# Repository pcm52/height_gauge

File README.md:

# height_gauge
Digital Height Gauge

Design files for digital height gauge as described on pcm52.com

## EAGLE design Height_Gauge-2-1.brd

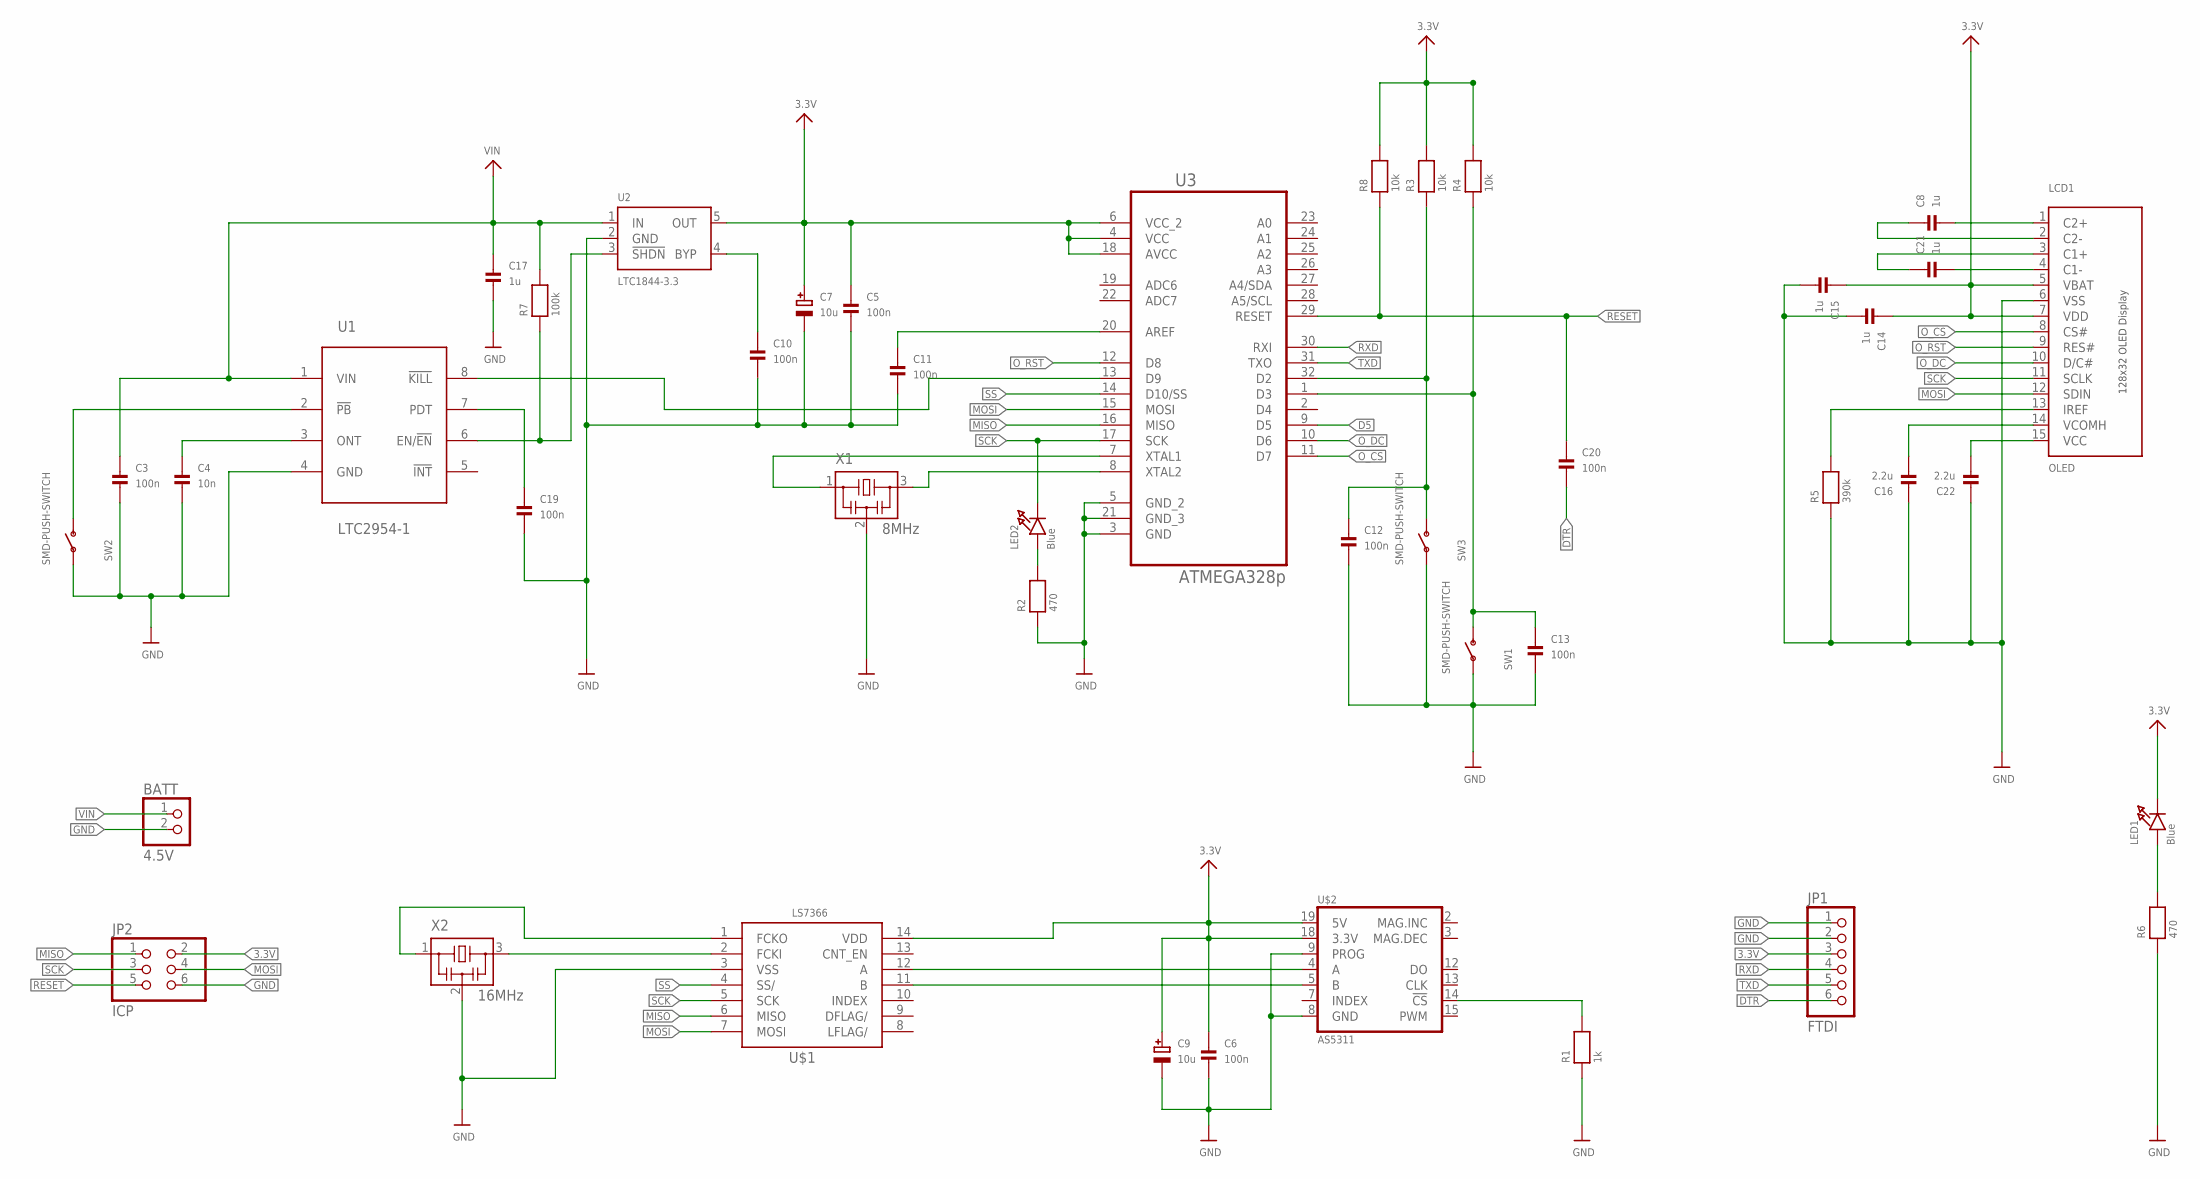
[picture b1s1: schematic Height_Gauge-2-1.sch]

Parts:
BATT: 4.5V; 1X02
C3, C5, C6, C10, C11, C12, C13, C19, C20: 100n; 0805
C4: 10n; 0805
C7, C9: 10u; EIA3216-18/A-W
C8, C14, C15, C17, C21: 1u; 0805
C16, C22: 2.2u; 0805
JP1: FTDI; 1X06-BIG
JP2: ICP; 2X03
LCD1: OLED; UG-2832HSWEG04_WRAPAROUND
LED1, LED2: Blue; CHIPLED_0805
R1: 1k; 0805
R2, R6: 470; 0805
R3, R4, R8: 10k; 0805
R5: 390k; 0805
R7: 100k; 0805
SW1, SW2, SW3: SMD-PUSH-SWITCH; PUSH-BUTTON-SMD
U1: LTC2954-1; TSOT23-8
U2: LTC1844-3.3; TSOT23-5
U3: ATMEGA328p; TQFP-32
U$1: LS7366; SO14
U$2: AS5311; TSSOP.20
X1: 8MHz; CSTCE-CRYSTAL-OSC
X2: 16MHz; CSTCE-CRYSTAL-OSC

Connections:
3.3V: C5.1, C6.1, C7.+, C9.+, C14.1, C15.1, JP1.3, JP2.2, LCD1.5 (VBAT), LCD1.7 (VDD), LED1.C, R3.2, R4.2, R8.2, U2.5 (OUT), U3.4 (VCC), U3.6 (VCC_2), U3.18 (AVCC), U$1.14 (VDD), U$2.18 (3.3V), U$2.19 (5V)
D5: U3.9 (D5)
DTR: C20.2, JP1.6
GND: BATT.2, C3.2, C4.2, C5.2, C6.2, C7.-, C9.-, C10.2, C11.2, C12.2, C13.2, C14.2, C15.2, C16.1, C17.2, C19.2, C22.1, JP1.1, JP1.2, JP2.6, LCD1.6 (VSS), R1.1, R2.1, R5.1, R6.1, SW1.P$1, SW2.P$1, SW3.P$1, U1.4 (GND), U2.2 (GND), U3.3 (GND), U3.5 (GND_2), U3.21 (GND_3), U$1.3 (VSS), U$2.8 (GND), U$2.9 (PROG), X1.2, X2.2
KILL: U1.8 (!KILL), U3.13 (D9)
MISO: JP2.1, U3.16 (MISO), U$1.6 (MISO)
MOSI: JP2.4, LCD1.12 (SDIN), U3.15 (MOSI), U$1.7 (MOSI)
unnamed: U$1.2 (FCKI), X2.3
unnamed: U$1.1 (FCKO), X2.1
unnamed: R7.1, U1.6 (EN/!EN), U2.3 (!SHDN)
unnamed: R1.2, U$2.14 (!CS)
unnamed: SW2.P$2 (S), U1.2 (!PB)
unnamed: U$1.12 (A), U$2.4 (A)
unnamed: U$1.11 (B), U$2.5 (B)
unnamed: C4.1, U1.3 (ONT)
unnamed: C10.1, U2.4 (BYP)
unnamed: C11.1, U3.20 (AREF)
unnamed: C12.1, R3.1, SW3.P$2 (S), U3.32 (D2)
unnamed: U3.7 (XTAL1), X1.1
unnamed: U3.8 (XTAL2), X1.3
unnamed: C13.1, R4.1, SW1.P$2 (S), U3.1 (D3)
unnamed: LED2.A, R2.2
unnamed: C8.2, LCD1.1 (C2+)
unnamed: LED1.A, R6.2
unnamed: C19.1, U1.7 (PDT)
unnamed: C8.1, LCD1.2 (C2-)
unnamed: C21.2, LCD1.4 (C1-)
unnamed: C21.1, LCD1.3 (C1+)
unnamed: LCD1.13 (IREF), R5.2
unnamed: C16.2, LCD1.14 (VCOMH)
unnamed: C22.2, LCD1.15 (VCC)
O_CS: LCD1.8 (CS#), U3.11 (D7)
O_DC: LCD1.10 (D/C#), U3.10 (D6)
O_RST: LCD1.9 (RES#), U3.12 (D8)
RESET: C20.1, JP2.5, R8.1, U3.29 (RESET)
RXD: JP1.4, U3.30 (RXI)
SCK: JP2.3, LCD1.11 (SCLK), LED2.C, U3.17 (SCK), U$1.5 (SCK)
SS: U3.14 (D10/SS), U$1.4 (SS/)
TXD: JP1.5, U3.31 (TXO)
VIN: BATT.1, C3.1, C17.1, R7.2, U1.1 (VIN), U2.1 (IN)

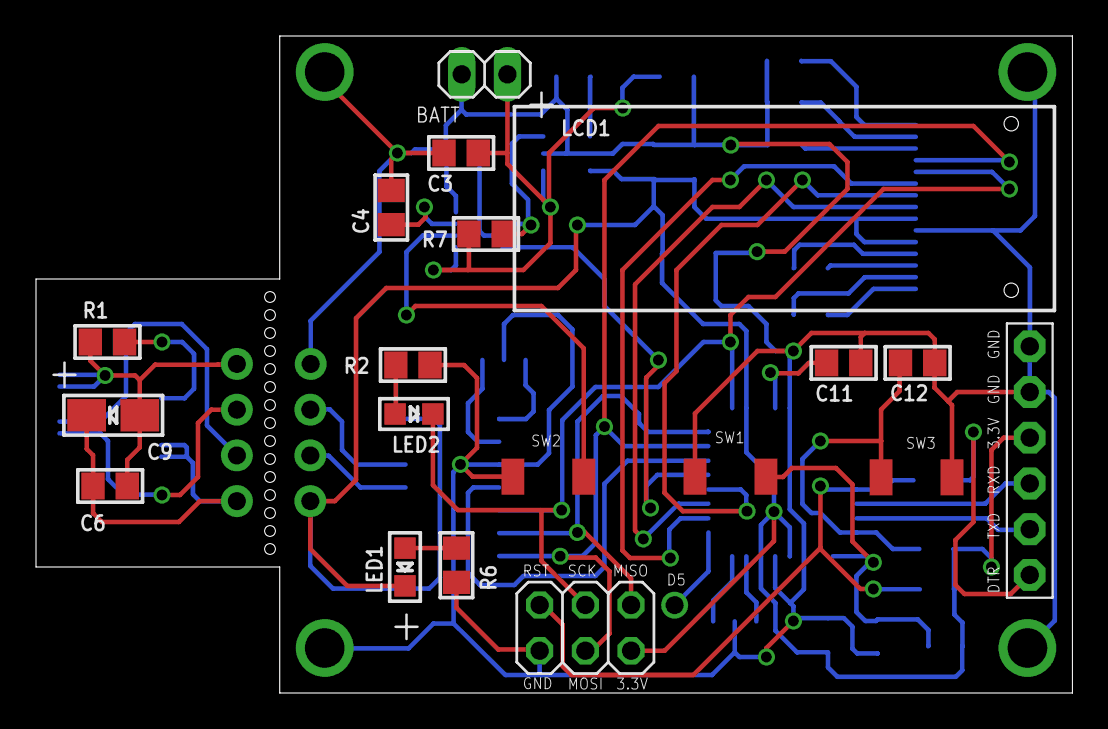
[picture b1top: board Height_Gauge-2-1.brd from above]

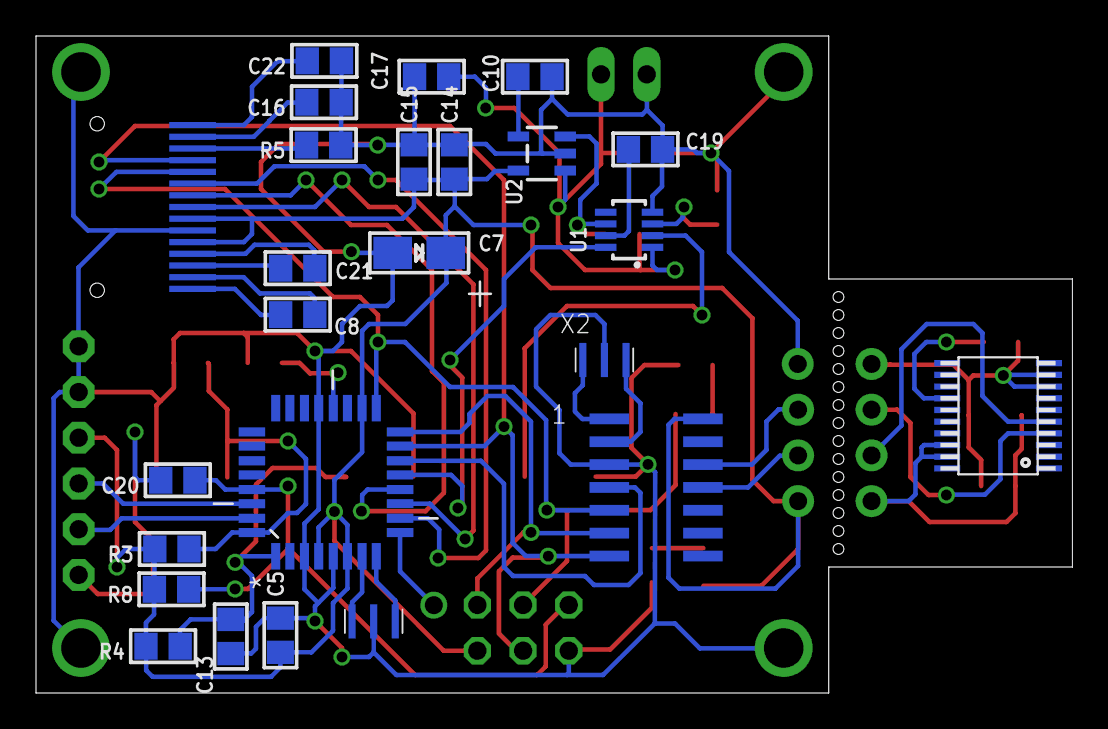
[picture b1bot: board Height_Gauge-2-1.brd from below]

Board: 2 copper layers, 57.6 x 36.5 mm, 43 parts (24 on the bottom side), 39 nets.

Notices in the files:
parts and their libraries:
microbuilder: This work is placed in the public domain, and may be freely used for commercial and non-commercial work with the following conditions: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
